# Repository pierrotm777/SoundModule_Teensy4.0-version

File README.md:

# Multi Sounds for RC boat (or Truck, Tank, Car and Plane)

## Credits
Based on a croby-b's code idea and powered by Rc-Navy libraries.  

## Outline of the documentation
1. Introduction (this page)
1. [Xany Compatibility](Xany_Compatibility.md)
1. [Xany Serial Commands](Xany_Mode.md)
1. [Buttons Serial Commands](Buttons_Mode.md)
1. [Wiring Sound module](Wiring_Module.md)
1. [Sd Card Structure](SD_Card_Structure.md)

## Introduction
For build this module we use the [Teensy-Variable-Playback](https://github.com/newdigate/teensy-variable-playback) library with a Teensy 4.0.  

This Sound Module is primarily intended for model boats, trucks, tractors, tanks, and backhoe loaders, but can also be configured for aircraft.  

This module can:  
- vary the engine sound based on engine speed.  
- use any type of engine sound (more than 10 are already available).  
- 4 simultaneous sounds in addition to the engine sound.  
- 16 pre-programmable sounds.  
- 4 pre-programmable random sounds.  
- volume control via the touchscreen, a button on the transmitter, or two buttons on a 10-button keypad.  
- Smoke system management (tank + air pump).  
- 5 RGB LEDs (multicolored).  
- Controllable via touchscreen or 10-button keypad.  
- 2W audio amplifier (useful for small boats or testing) or 18W.  
- Controllable via a receiver with PWM, CPPM, SBUS (Frsky or others), IBUS (Flysky), SRXL (Multiplex), SUMD (Graupner), JETI, or CRSF (ExpressLRS/TBS) output.  
- ESC output management to adjust engine sound (adjustable acceleration and deceleration).  
- 4 alarms, one of which is reversible to detect the absence of liquid, for example.  
- Telemetry feedback of the Teensy's temperature as well as the motor battery voltage for Frsky (Hub or S-Port), Flysky (Ibus), ExpressLRS/TBS (CRSF).  
- Module management/configuration via its serial interface.  
- Module configuration backup on an SD card.  

SD Card:  
- This contains all the sounds and the sound module's configuration.  

Power Supply:  
The module is powered by a Lipo battery for a maximum of 2s to 3s.  
It is possible to enable or disable the module's power supply using a relay or other solution via the On/Off connector.  

A custom printed circuit board has been created. We are currently at version v1.2, visible above.  
A v1.3 version is planned, which will include an additional option via an I2C interface.  

Creating a new engine sound:  
Simply retrieve the desired engine sound to create a startup sound, an operating sound, and a shutdown sound.  
The more realistic the original sound, the more appealing the result will be.  
So, when the engine starts, you hear the typical sound of an engine hesitating, followed by the normal sound with variations in frequency and speed.  
Then, when the engine stick returns to center, after 5 to 10 seconds (adjustable), the shutdown sound is played.  

## Two modes
Two modes are possibles:
- Use [X-Any/BURC encoder](https://p-loussouarn-free-fr.translate.goog/arduino/exemple/RCUL/RCUL.html?_x_tr_sch=http&_x_tr_sl=auto&_x_tr_tl=en&_x_tr_hl=en) fonctions by RC-Navy, thanks to him.  
- Use [Buttons Keypad](http://p.loussouarn.free.fr/projet/MS8-V2/MS8-V2.html#Keyboard) fonctions by RC-Navy, thanks to him.  
- The module read all WAV sounds from a SD card (from /ENGINES folder).  

You can find more informations on the Sound Module:
- [french manual](https://github.com/pierrotm777/SoundModule_Teensy4.0-version/blob/main/Module_Son_Manuel_Utilisateur.pdf).  
- [english manual (TODO)](https://github.com/pierrotm777/SoundModule_Teensy4.0-version/blob/main/Module_Son_Manuel_Utilisateur.pdf).    

### X-Any mode
This mode decode the X-Any/BURC stream.  

Depending on the receiver used, it's possible to connect the sound module in different ways:  
- PWM  
- CPPM  
- SBUS (without inverter)  
- IBUS  
- SUMD  
- SRXL  
- JETIEX  
- CRSF  

A [BURC encoder](https://github.com/pierrotm777/BURC_Encoder) or a [LVGL ESP32 S3 Screen](https://github.com/pierrotm777/ESP32-BURC-Screen) is connected on a Handset by CPPM or SBUS.     

These X-Any/BURC coder use the **trainer port** as slave and use up to 2 channels (for the Sound Module) as X-Any fonctions.  
X-Any inject three additionals RC channels to a CPPM or SBUS frame for transport messages over these additionals channels.  
At reception side, these messages are extracted from these 2 channels corresponding to the additionals channels.  
These 2 channels are used to transport 2 messages containing the status of a set of switches or set of sound in the Sound Modul case.  

### Buttons mode
This mode use a keyboard with 10 buttons (8 buttons + 2 for volume sounds).  
It's a good solution for old rc transmitters that do not have a training input.  
This keyboard is connected on a free input channel in place of a potentiometer.  
This mode accept only 8 sounds.  
The buttons 9 and 10 up or down the volume's sounds.  

<table cellspacing=0>
  <tr>
    <td align=center width=400><br><b>KeyBoard 10 buttons</td>
  </tr>
</table>

Depending on the receiver used, it's possible to connect the sound module in different ways:  
- PWM  
- CPPM  
- SBUS (without inverter)  
- IBUS  
- SUMD  
- SRXL  
- JETIEX  
- CRSF  

## PCB versions
<table cellspacing=0>
  <tr>
    <td align=center width=400><br><b>V1.0 (deprecated)</td>
    <td align=center width=400><br><b>V1.1 (deprecated)</td>
    <td align=center width=400><br><b>V1.2</td>
	<td align=center width=400><br><b>V1.3</td>
  </tr>
</table>

## WAV Sounds
Play **16-bit PCM 44100Hz Stereo** WAV audio samples at variable playback rates on Teensy.  
- Note : this library only works with signed 16-bit integer samples. Floating point samples will not play.  
- For best performance, use SDXC UHS 30MB/sec Application Performance Class 2 (A2) class micro SD-card.  

### Sounds Motor
It's possible to select several motors.  
The module can list all sound's motor found into the SD card [ENGINES folder](https://github.com/pierrotm777/SoundModule_Teensy4.0-version/tree/main/SD_Wav_Files/ENGINES).  
**ENG.LIST = DSL-LTL, DSL-V12, VAPEUR, DSL-OLD, DSL-120, DSL-TURB, DSL-TUG, SCAN-V12, DSL-BIG, DSL-180, DIESEL7, SCAN-250, CAT-C32, BF109**  
Each motor use:  
- A start file, ex:DSL-LTL_STA.  
- An idle file, ex:DSL-LTL_IDL.  
- A stop file, ex:DSL-LTL_STP.  

It's possible to add new motor's sounds.  
The better way, for me, is to use [Audacity](https://www.audacityteam.org) for cut all sound find and save it as 16bits PCM 44100Hz wav file.  

### All other sounds
All other other sounds will have to be copied under the main path.  
See our sounds [here](https://github.com/pierrotm777/SoundModule_Teensy4.0-version/tree/main/SD_Wav_Files).  
You can change the **USER1.wav to USER15.wav by your own sounds**.  
USER16.wav is used as alarms sound.  

## Upload a firmware
Only one firmware for all features:
1. For PCB v1.2:  
  - [teensy_sound_Xany_V3_9.hex](https://github.com/pierrotm777/SoundModule_Teensy4.0-version/blob/main/Firmware/teensy_sound_Xany_V3_9-v1.2.hex)  
1. For PCB v1.3:
  - [teensy_sound_Xany_V3_9.hex](https://github.com/pierrotm777/SoundModule_Teensy4.0-version/blob/main/Firmware/teensy_sound_Xany_V3_9-v1.3.hex)  
For upload a firmware into the Teensy you must to use the [Teensy Loader](https://github.com/pierrotm777/SoundModule_Teensy4.0-version/tree/main/Firmware/Teensy_Uploader.zip).  

# New features

## Wifi feature
With the v1.2 and v1.3 PCB versions, it's now possible to obtain several informations from the sound module.  
For use this option, we need to add a little [ESP32C3 LCD board](https://www.google.com/search?client=firefox-b-d&q=ESP32C3+LCD) connected to the Teensy bu a serial port.  
This board use the ESPNOW protocol for communicate with the [ESP32 coder](https://github.com/pierrotm777/ESP32-BURC-Screen) screen.  
See [here]() for more informations.  

## Temperatures feature
With the v1.2 and v1.3 PCB versions, it's now possible to send telemetry to a RC transmitter.  
Three sensors are simulated:
  - Battery of your model, (by default 3S with R12=33K (PCB v1.2) or R9=33K (PCB v1.3).  
  - Teensy temperature (no need specific hardware).  
  - Tank temperature (need to connect a DS18B20 to Teensy pin 27, GND and 3.3v).  
   
  Versions telemetries usable are:
    - S-PORT (D16 Frsky)  
    - HUB (old D8 Frsky)  
    - IBUS   
    - MLINK  
    - HOTT  
    - JETIEX  
    - CRSF

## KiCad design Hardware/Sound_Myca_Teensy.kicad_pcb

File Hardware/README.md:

# Hardwares
My PCB use Kicad 9.0.  

## Schematics
<table border="2">
<tr>
<td></td>
<td></td>
</tr>
</table>

## PCB
<table border="2">
<tr>
<td></td>
<td></td>
</tr>
</table>

# Firmwares
Two modes are possibles:
- X-Any.
- Buttons Keypad.

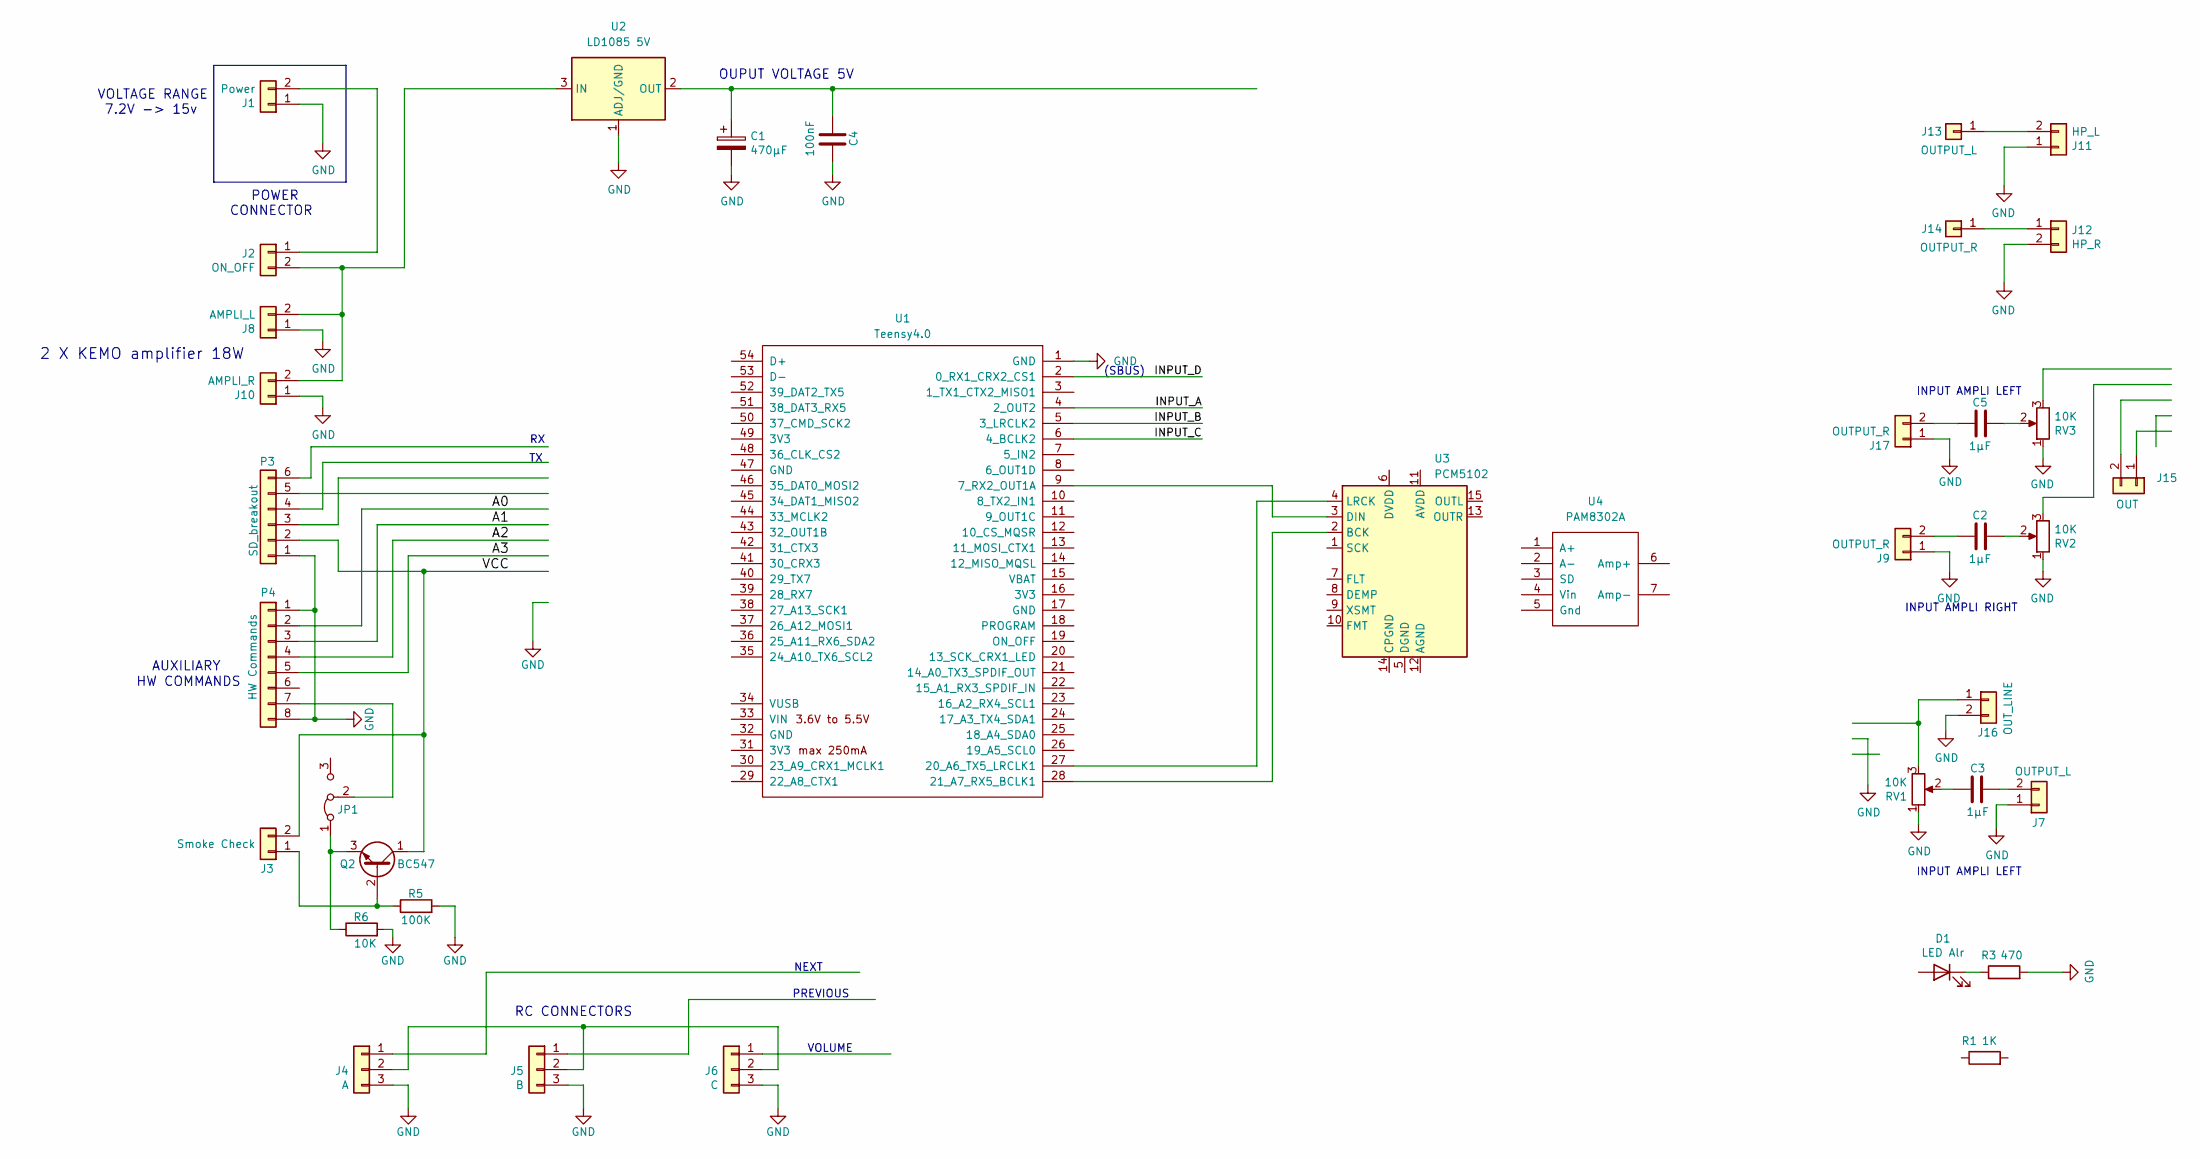
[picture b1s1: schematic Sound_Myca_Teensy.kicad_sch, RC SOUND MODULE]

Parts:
C1: 470µF; C_Radial_D8.0mm_H11.5mm_P3.50mm
C2, C3, C5: 1µF; C_Disc_D5.0mm_W2.5mm_P5.00mm
C4: 100nF; C_Disc_D5.0mm_W2.5mm_P5.00mm
D1: LED Alr; LED_D3.0mm
J1: Power; bornier2
J2: ON_OFF; bornier2
J3: Smoke Check; PinHeader_1x02_P2.54mm_Vertical
J4: A; PinHeader_1x03_P2.54mm_Vertical
J5: B; PinHeader_1x03_P2.54mm_Vertical
J6: C; PinHeader_1x03_P2.54mm_Vertical
J7: OUTPUT_L; bornier2
J8: AMPLI_L; bornier2
J9, J17: OUTPUT_R; bornier2
J10: AMPLI_R; bornier2
J11: HP_L; bornier2
J12: HP_R; bornier2
J13: OUTPUT_L; bornier1
J14: OUTPUT_R; bornier1
J15: OUT; PinHeader_2x01_P2.54mm_Vertical
J16: OUT_LINE; PinHeader_2x01_P2.54mm_Vertical
JP1: Jumper_2_Open; PinHeader_1x03_P2.54mm_Vertical
P3: SD_breakout; SD_BREAKOUT_MINI
P4: HW Commands; PinHeader_1x08_P2.54mm_Vertical
Q2: BC547; TO-92_Inline
R1: 1K; R_Axial_DIN0204_L3.6mm_D1.6mm_P7.62mm_Horizontal
R3: 470; R_Axial_DIN0204_L3.6mm_D1.6mm_P7.62mm_Horizontal
R5: 100K; R_Axial_DIN0204_L3.6mm_D1.6mm_P7.62mm_Horizontal
R6: 10K; R_Axial_DIN0204_L3.6mm_D1.6mm_P7.62mm_Horizontal
RV1, RV2, RV3: 10K; Potentiometer_Round_5.08x5.08_Vertical
U1: Teensy4.0; Teensy40
U2: LD1085 5V; TO-220-3_Horizontal_TabDown
U3: PCM5102; pcm5102
U4: PAM8302A; pam8302a

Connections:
/A0: P4.2
/A1: P4.3
/A2: P4.4
/A3: P4.5
/INPUT_A: U1.4 (2_OUT2)
/INPUT_B: U1.5 (3_LRCLK2)
/INPUT_C: U1.6 (4_BCLK2)
/INPUT_D: U1.2 (0_RX1_CRX2_CS1)
/VCC: J3.2, P3.2, Q2.1 (C)
GND: C1.2, C4.1, J1.1, J4.3, J5.3, J6.3, J7.1, J8.1, J9.1, J10.1, J11.1, J12.2, J16.2, J17.1, P3.1, P4.1, P4.8, R3.2, R5.2, R6.2, RV1.1, RV2.1, RV3.1, U1.1 (GND), U2.1 (ADJ/GND)
unnamed: C2.1, RV2.2
unnamed: C3.1, RV1.2
unnamed: C5.1, RV3.2
unnamed: D1.1 (K), R3.1
unnamed: J1.2, J2.1
unnamed: J3.1, Q2.2 (B), R5.1
unnamed: J4.2, J5.2, J6.2
unnamed: C3.2, J7.2
unnamed: C2.2, J9.2
unnamed: J2.2, J8.2, J10.2, U2.3 (IN)
unnamed: J11.2, J13.1
unnamed: J12.1, J14.1
unnamed: J16.1, RV1.3
unnamed: C5.2, J17.2
unnamed: JP1.1 (A), Q2.3 (E), R6.1
unnamed: JP1.2 (C), P4.7
unnamed: U1.9 (7_RX2_OUT1A), U3.3 (DIN)
unnamed: U1.27 (20_A6_TX5_LRCLK1), U3.4 (LRCK)
unnamed: U1.28 (21_A7_RX5_BCLK1), U3.2 (BCK)
unnamed: C1.1, C4.2, U2.2 (OUT)

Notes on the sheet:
2 X KEMO amplifier 18W
AUXILIARY
INPUT AMPLI LEFT
OUPUT VOLTAGE 5V
VOLUME
INPUT AMPLI RIGHT
(SBUS)
NEXT
POWER CONNECTOR
RC CONNECTORS
PREVIOUS
VOLTAGE RANGE 7.2V -> 15v
HW COMMANDS

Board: 2 copper layers, 38 parts (1 on the bottom side), 22 nets, no tracks yet.

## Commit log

2025-02-10 Add Wav files
    Wav files to copy on a SD card
2025-02-10 Add first Kicad PCB
2025-02-23 Create ENGINES.zip
    Add engine's sound in 16bits PCM Stereo wav files
2025-03-01 Add 3d pictures
2025-03-02 Update Kicad files
2025-03-02 Update again
2025-03-02 Add doc, 10 buttons keyboard and kemo
2025-03-02 update
    - add buttons page
    - update main README.md file
2025-03-02 Update WAV files
2025-03-02 Add firmware and upload method
2025-03-02 Updates
    - update kicad files
    - add gerber v1.0
    - add bom
2025-03-10 rename first pcb to v1.0
2025-03-10 move to v1.0
2025-03-10 add v1.1
2025-03-11 update readme files
2025-03-11 other update
2025-03-11 add wire info
2025-03-14 add bom
2025-03-15 add divider on pin 15
2025-03-26 update pcb
2025-03-26 add gerber and bom
2025-03-29 add v1.2
2025-04-05 update pictures
2025-04-09 update top,bottom
2025-04-11 update mod lipo add
2025-04-13 add details systems
2025-04-14 update xany tests
2025-04-17 update top and bom
2025-04-19 update firmwares add pictures
2025-04-24 add alarms sounds
2025-04-24 add some pictures
2025-04-24 change
2025-04-24 change again
2025-04-24 add wiring
2025-04-25 update exel file
2025-04-29 add tank and blower
2025-04-29 adds
2025-04-29 add alarms
2025-04-29 add power
2025-04-29 add telemetry
2025-05-03 update fimware
2025-05-06 add 1st v1.3
2025-05-22 Add all my sounds
2025-05-24 update firmware
2025-05-24 add pdf manual
2025-05-25 update Rcul tests
2025-12-18 Update v1.3 board
2025-12-19 Add 3.9 version
2025-12-19 rename firmware files
2025-12-19 remove v1.2 firmware
2025-12-20 add 18b20 wiring
2025-12-20 add ds18b20 to teensy
2026-02-15 update RCUL table
2026-02-15 correction
2026-05-07 Add Radiomaster ER8
